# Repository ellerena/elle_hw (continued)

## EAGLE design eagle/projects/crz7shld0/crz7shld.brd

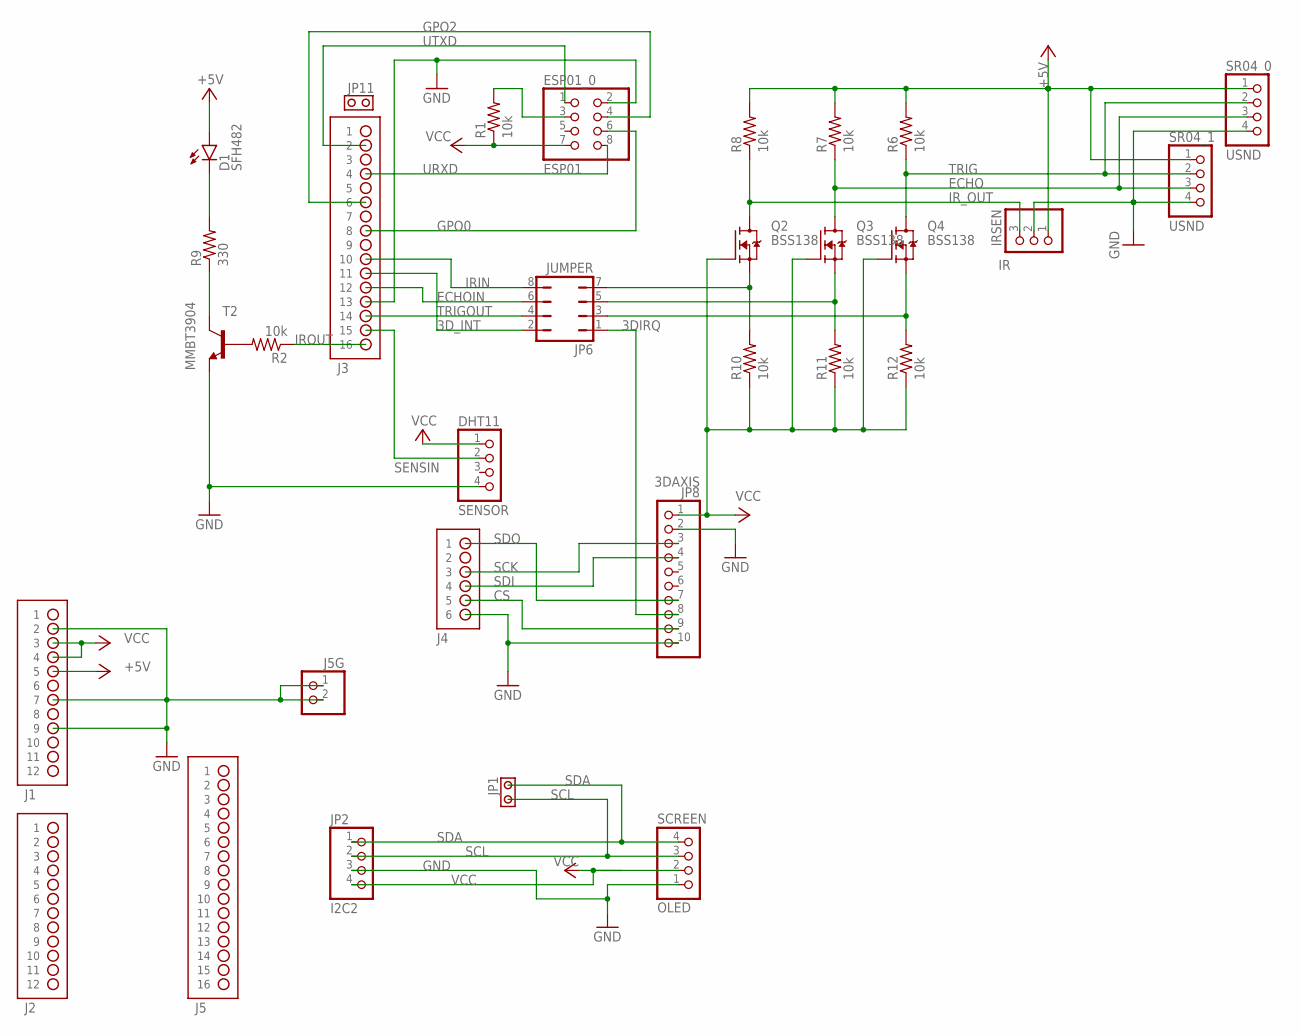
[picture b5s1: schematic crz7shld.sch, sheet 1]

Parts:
D1: SFH482
DHT11: SENSOR; 1X04
ESP01_0: ESP01; 2X04
IR: IRSEN; 1X03
J1, J2: HDR-2X6
J3, J5: HDR-2X8
J4: HDR-2X3
J5G: PINHD-1X2; 1X02
JP1, JP11: JPR-1X2
JP2: I2C2; 1X04
JP6: JUMPER; JP4Q
JP8: 3DAXIS; 1X10
OLED: SCREEN; 1X04
Q2, Q3, Q4: BSS138; SOT23
R1, R2, R6, R7, R8, R10, R11, R12: 10k; R0402
R9: 330; R0402
SR04_0, SR04_1: USND; 1X04
T2: MMBT3904; SOT23-BEC

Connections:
3DIRQ: JP6.1, JP8.8
3D_INT: J3.11, JP6.2
+5V: D1.A, IR.1, J1.5, R6.2, R7.2, R8.2, SR04_0.1, SR04_1.1
CS: J4.5, JP8.9
ECHO: Q3.3 (D), R7.1, SR04_0.3, SR04_1.3
ECHOIN: J3.12, JP6.6
GND: DHT11.4, ESP01_0.2, IR.2, J1.2, J1.7, J1.9, J3.13, J4.6, J5G.1, J5G.2, JP2.3, JP8.2, JP8.10, OLED.1, SR04_0.4, SR04_1.4, T2.E
GPO0: ESP01_0.6, J3.8
GPO2: ESP01_0.4, J3.6
IRIN: J3.10, JP6.8
IROUT: J3.16, R2.1
IR_OUT: IR.3, Q2.3 (D), R8.1
unnamed: D1.K (C), R9.2
unnamed: JP6.7, Q2.2 (S), R10.2
unnamed: R2.2, T2.B
unnamed: ESP01_0.3, R1.2
unnamed: JP6.5, Q3.2 (S), R11.2
unnamed: JP6.3, Q4.2 (S), R12.2
unnamed: R9.1, T2.C
SCK: J4.3, JP8.3
SCL: JP1.1, JP2.2, OLED.3
SDA: JP1.2, JP2.1, OLED.4
SDI: J4.4, JP8.4
SDO: J4.1, JP8.7
SENSIN: DHT11.2, J3.15
TRIG: Q4.3 (D), R6.1, SR04_0.2, SR04_1.2
TRIGOUT: J3.14, JP6.4
URXD: ESP01_0.8, J3.4
UTXD: ESP01_0.1, J3.2
VCC: DHT11.1, ESP01_0.7, J1.3, J1.4, JP2.4, JP8.1, OLED.2, Q2.1 (G), Q3.1 (G), Q4.1 (G), R1.1, R10.1, R11.1, R12.1

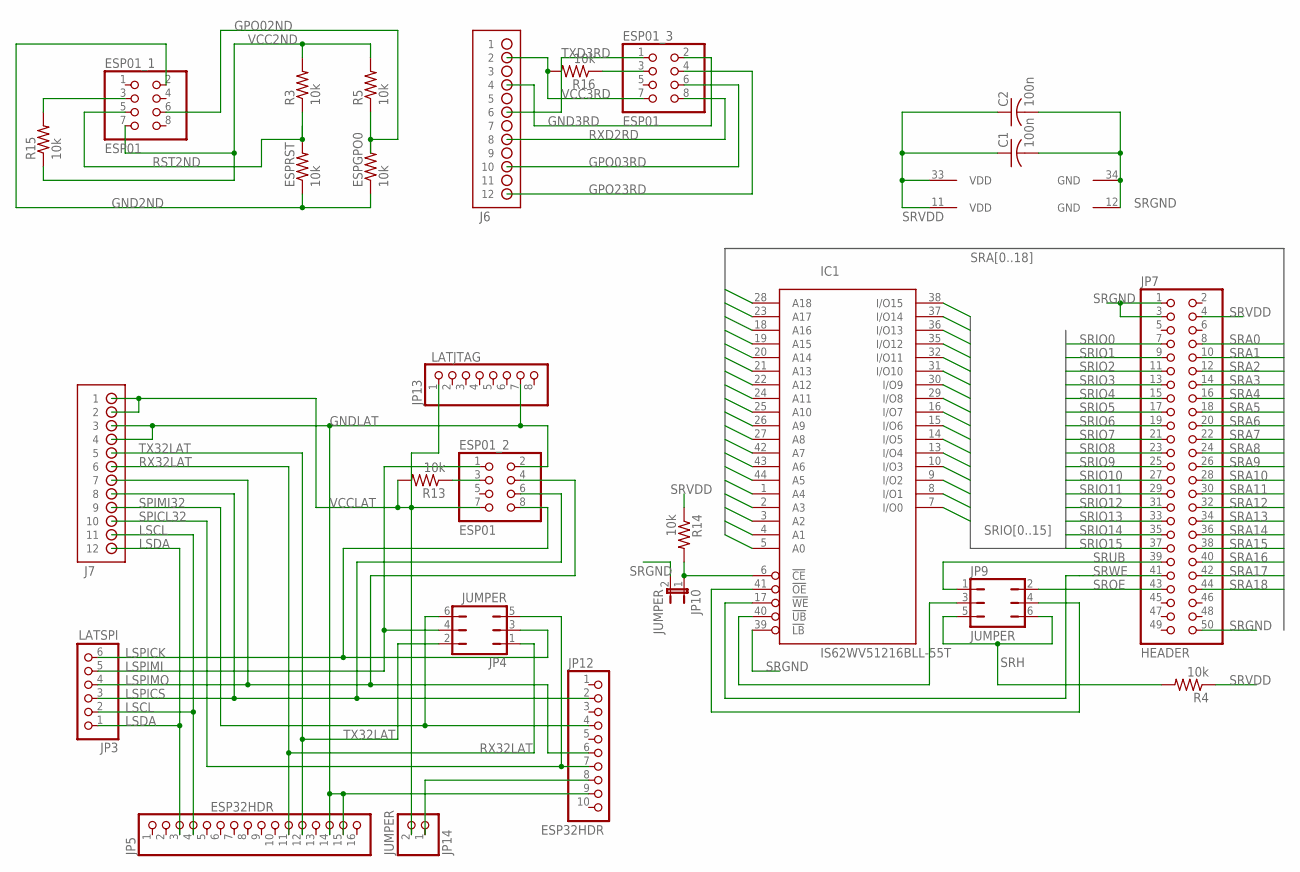
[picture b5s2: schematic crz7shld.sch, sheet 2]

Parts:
C1, C2: 100n; C0402
ESP01_1, ESP01_2, ESP01_3: ESP01; 2X04
ESPGPO0: 10k; 0204/5
ESPRST: 10k; 0204/5
IC1: IS62WV51216BLL-55T; TSOP-II-44
J6, J7: HDR-2X6
JP3: LATSPI; 1X06
JP4, JP9: JUMPER; JP3Q
JP5: ESP32HDR; 1X16
JP7: HEADER; 2X25
JP10: JUMPER; JP1
JP12: ESP32HDR; 1X10
JP13: LATJTAG; 1X08
JP14: JUMPER; 1X02
R3, R4, R5, R13, R14, R15, R16: 10k; R0402

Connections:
GND2ND: ESP01_1.2, ESPGPO0.1, ESPRST.1
GND3RD: ESP01_3.2, J6.4
GNDLAT: ESP01_2.2, J7.3, J7.4, JP5.14, JP5.15, JP12.9, JP13.7
GPO02ND: ESP01_1.6, ESPGPO0.2, R5.1
GPO03RD: ESP01_3.6, J6.10
GPO23RD: ESP01_3.4, J6.12
LSCL: J7.11, JP3.2, JP5.4
LSDA: J7.12, JP3.1, JP5.3
LSPICK: ESP01_2.8, JP3.6, JP4.3
LSPICS: ESP01_2.6, J7.8, JP3.3, JP12.2
LSPIMI: ESP01_2.1, JP3.5, JP4.4
LSPIMO: ESP01_2.4, J7.7, JP3.4, JP12.6
unnamed: IC1.41 (!OE), JP9.4
unnamed: JP12.8, JP14.1
unnamed: IC1.40 (!UB), JP9.3
unnamed: ESP01_2.3, R13.1
unnamed: ESP01_1.3, R15.2
unnamed: ESP01_3.3, R16.1
unnamed: IC1.6 (!CE), JP10.1, R14.2
RST2ND: ESP01_1.5, ESPRST.2, R3.1
RX32LAT: J7.6, JP4.1, JP5.11
RXD2RD: ESP01_3.8, J6.8
SPICL32: J7.10, JP4.5, JP12.7
SPIMI32: J7.9, JP4.6, JP12.4
SRA0: IC1.5 (A0), JP7.8
SRA1: IC1.4 (A1), JP7.10
SRA2: IC1.3 (A2), JP7.12
SRA3: IC1.2 (A3), JP7.14
SRA4: IC1.1 (A4), JP7.16
SRA5: IC1.44 (A5), JP7.18
SRA6: IC1.43 (A6), JP7.20
SRA7: IC1.42 (A7), JP7.22
SRA8: IC1.27 (A8), JP7.24
SRA9: IC1.26 (A9), JP7.26
SRA10: IC1.25 (A10), JP7.28
SRA11: IC1.24 (A11), JP7.30
SRA12: IC1.22 (A12), JP7.32
SRA13: IC1.21 (A13), JP7.34
SRA14: IC1.20 (A14), JP7.36
SRA15: IC1.19 (A15), JP7.38
SRA16: IC1.18 (A16), JP7.40
SRA17: IC1.23 (A17), JP7.42
SRA18: IC1.28 (A18), JP7.44
SRGND: C1.2, C2.2, IC1.12 (GND), IC1.34 (GND), IC1.39 (!LB), JP7.1, JP7.3, JP7.50, JP10.2
SRH: JP9.5, JP9.6, R4.2
SRIO0: IC1.7 (I/O0), JP7.7
SRIO1: IC1.8 (I/O1), JP7.9
SRIO2: IC1.9 (I/O2), JP7.11
SRIO3: IC1.10 (I/O3), JP7.13
SRIO4: IC1.13 (I/O4), JP7.15
SRIO5: IC1.14 (I/O5), JP7.17
SRIO6: IC1.15 (I/O6), JP7.19
SRIO7: IC1.16 (I/O7), JP7.21
SRIO8: IC1.29 (I/O8), JP7.23
SRIO9: IC1.30 (I/O9), JP7.25
SRIO10: IC1.31 (I/O10), JP7.27
SRIO11: IC1.32 (I/O11), JP7.29
SRIO12: IC1.35 (I/O12), JP7.31
SRIO13: IC1.36 (I/O13), JP7.33
SRIO14: IC1.37 (I/O14), JP7.35
SRIO15: IC1.38 (I/O15), JP7.37
SROE: JP7.43, JP9.2
SRUB: JP7.39, JP9.1
SRVDD: C1.1, C2.1, IC1.11 (VDD), IC1.33 (VDD), JP7.4, R4.1, R14.1
SRWE: IC1.17 (!WE), JP7.41
TX32LAT: J7.5, JP4.2, JP5.12
TXD3RD: ESP01_3.1, J6.6
VCC2ND: ESP01_1.7, R3.2, R5.2, R15.1
VCC3RD: ESP01_3.7, J6.2, R16.2
VCCLAT: ESP01_2.7, J7.1, J7.2, JP13.1, JP14.2, R13.2

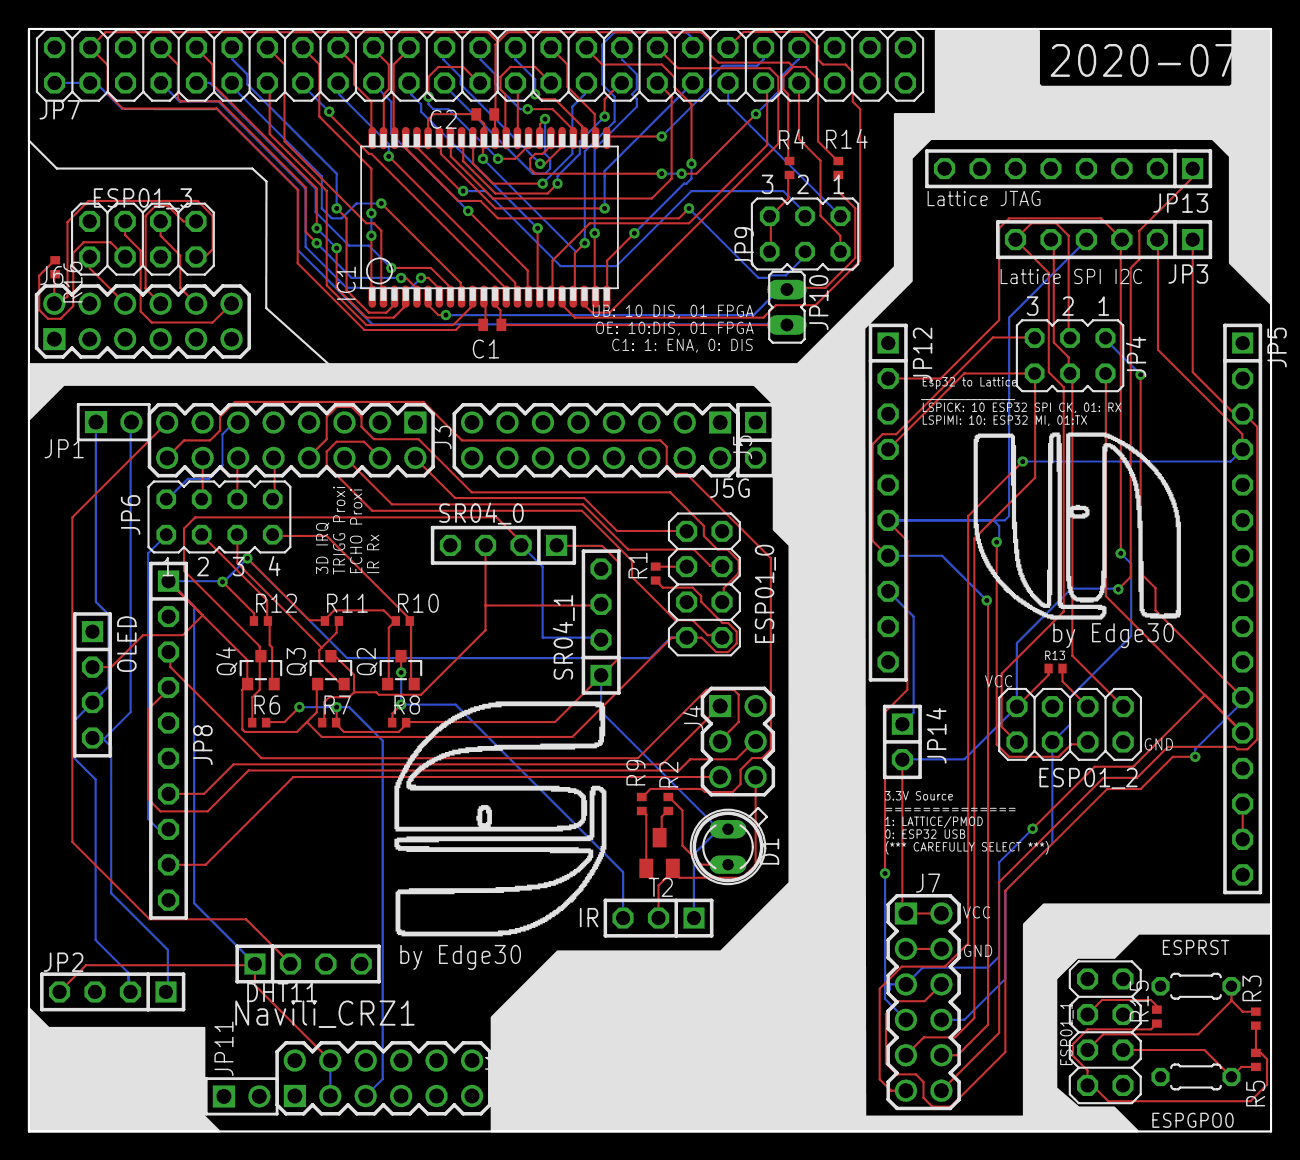
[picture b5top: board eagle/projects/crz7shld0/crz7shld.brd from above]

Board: 2 copper layers, 89.0 x 79.0 mm, 57 parts (0 on the bottom side), 100 nets.

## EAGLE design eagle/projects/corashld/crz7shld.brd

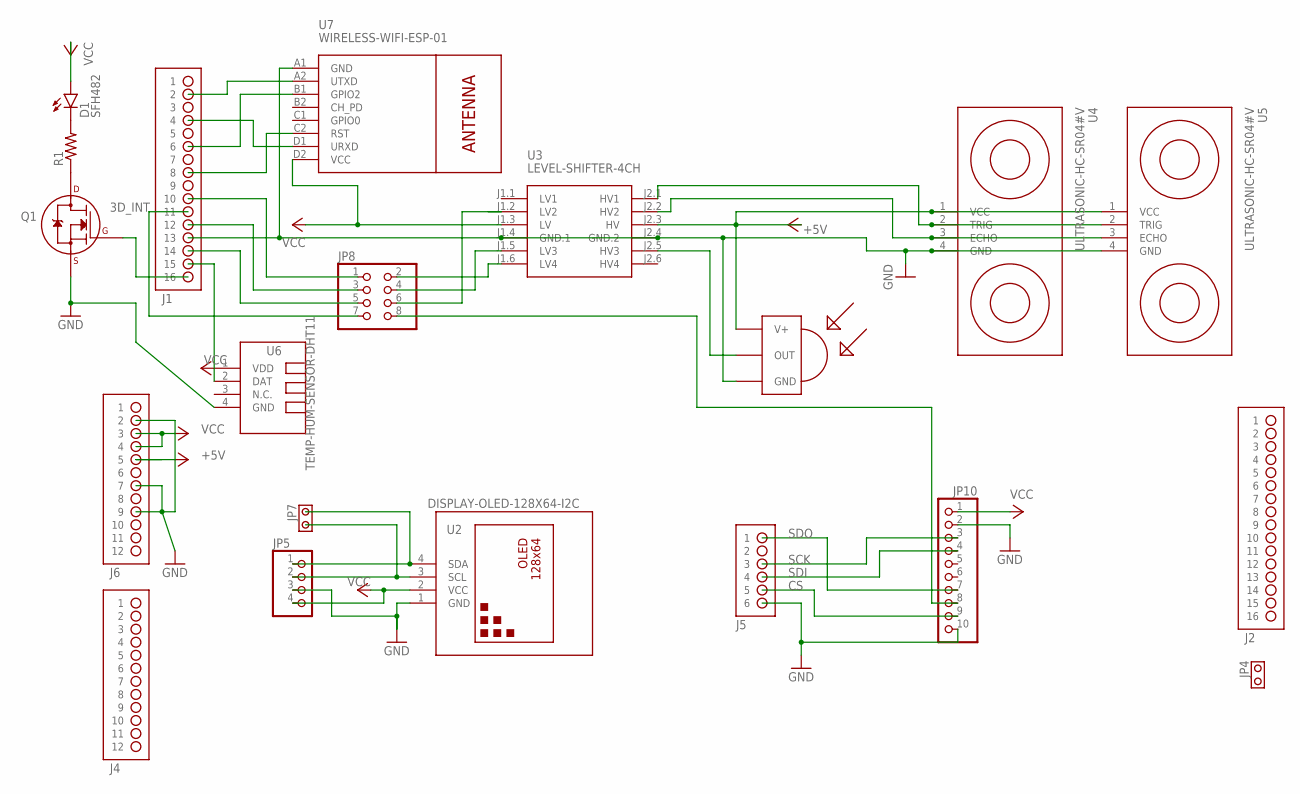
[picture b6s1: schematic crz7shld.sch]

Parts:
D1: SFH482
J1, J2: HDR-2X8
J4, J6: HDR-2X6
J5: HDR-2X3
JP4, JP7: JPR-1X2
JP5: PINHD-1X4; 1X04
JP8: PINHD-2X4; 2X04
JP10: PINHD-1X10; 1X10
Q1: 2N7000_TO92; TO-92
R1: R-US_0204/5; 0204/5
U1: TSOP1833; TSOP18XX
U2: DISPLAY-OLED-128X64-I2C
U3: LEVEL-SHIFTER-4CH
U4, U5: ULTRASONIC-HC-SR04#V
U6: TEMP-HUM-SENSOR-DHT11
U7: WIRELESS-WIFI-ESP-01

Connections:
3D_INT: J1.11, JP8.7
+5V: J6.5, U1.VCC (V+), U3.J2.3 (HV), U4.1 (VCC), U5.1 (VCC)
CS: J5.5, JP10.9
GND: J1.13, J5.6, J6.2, J6.7, J6.9, JP5.3, JP10.2, JP10.10, Q1.1 (S), U1.GND, U2.1 (GND), U3.J1.4 (GND.1), U3.J2.4 (GND.2), U4.4 (GND), U5.4 (GND), U6.4 (GND), U7.A1 (GND)
unnamed: D1.K (C), R1.2
unnamed: Q1.3 (D), R1.1
unnamed: J1.16, Q1.2 (G)
unnamed: U3.J2.2 (HV2), U4.3 (ECHO), U5.3 (ECHO)
unnamed: J1.14, JP8.5
unnamed: J1.12, JP8.3
unnamed: U1.OUT, U3.J2.5 (HV3)
unnamed: U3.J2.1 (HV1), U4.2 (TRIG), U5.2 (TRIG)
unnamed: J1.10, JP8.1
unnamed: JP8.2, U3.J1.6 (LV4)
unnamed: JP8.4, U3.J1.5 (LV3)
unnamed: JP8.6, U3.J1.2 (LV2)
unnamed: J1.15, U6.2 (DAT)
unnamed: J1.2, U7.A2 (UTXD)
unnamed: J1.4, U7.D1 (URXD)
unnamed: J1.6, U7.B1 (GPIO2)
unnamed: J1.8, U7.C2 (RST)
unnamed: JP8.8, JP10.8
SCK: J5.3, JP10.3
SCL: JP5.2, JP7.1, U2.3 (SCL)
SDA: JP5.1, JP7.2, U2.4 (SDA)
SDI: J5.4, JP10.4
SDO: J5.1, JP10.7
VCC: D1.A, J6.3, J6.4, JP5.4, JP10.1, U2.2 (VCC), U3.J1.3 (LV), U6.1 (VDD), U7.D2 (VCC)

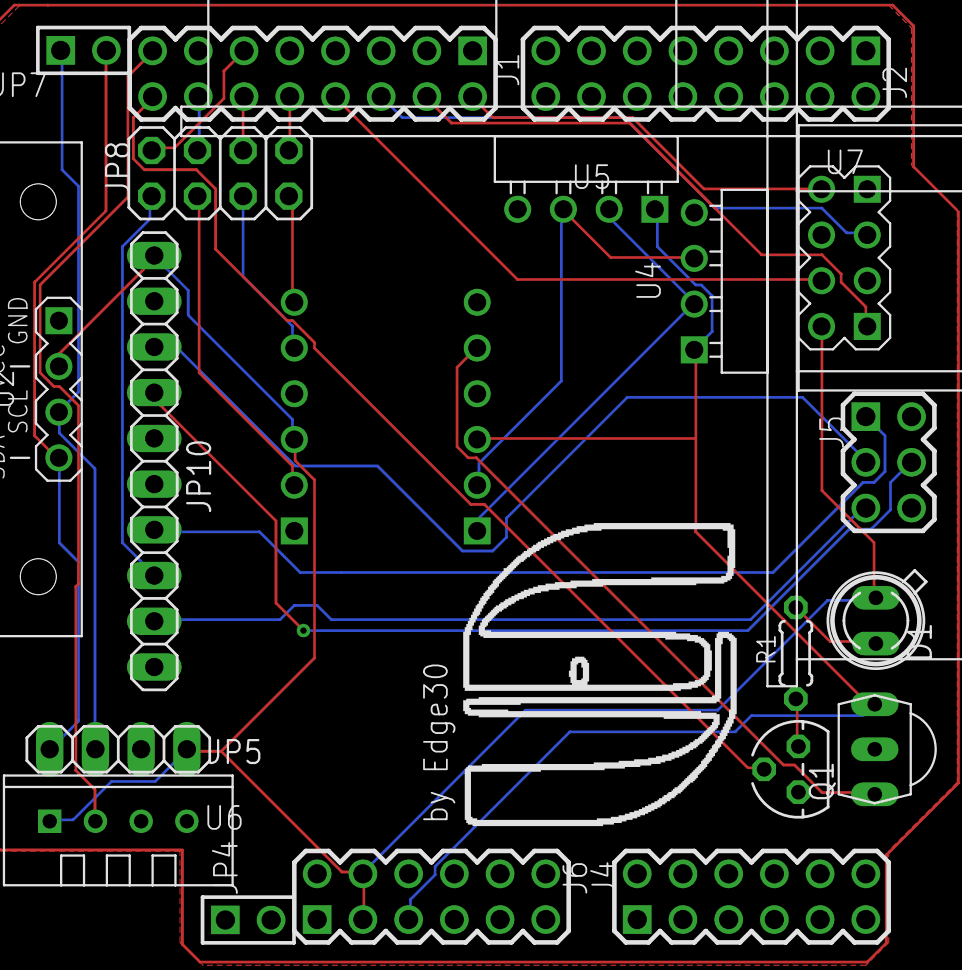
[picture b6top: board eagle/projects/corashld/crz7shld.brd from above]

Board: 2 copper layers, 20 parts (1 on the bottom side), 28 nets.

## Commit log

2020-07-23 001 for jlcpcb Multi board Cora z7 utility shield
2020-07-24 Order JLCPCB
2020-09-06 order JLCPCB crz7shld1
2020-10-20 Post build changes.
2021-09-15 crz7shlda0 - production 09/12/2021
2021-09-24 gitignore
2021-10-09 Cmod A7 shield to be sent for production
2021-10-09 Cmod A7 - FIX previous commit which was faulty
2021-11-27 cmod7shld0, crz7shlda0 production
2021-11-27 update git ignore to add csv.
2022-01-09 Production 01-2022 - esp32md1 and mk1 dil24
2024-07-09 just push latest hanging changes to repo
